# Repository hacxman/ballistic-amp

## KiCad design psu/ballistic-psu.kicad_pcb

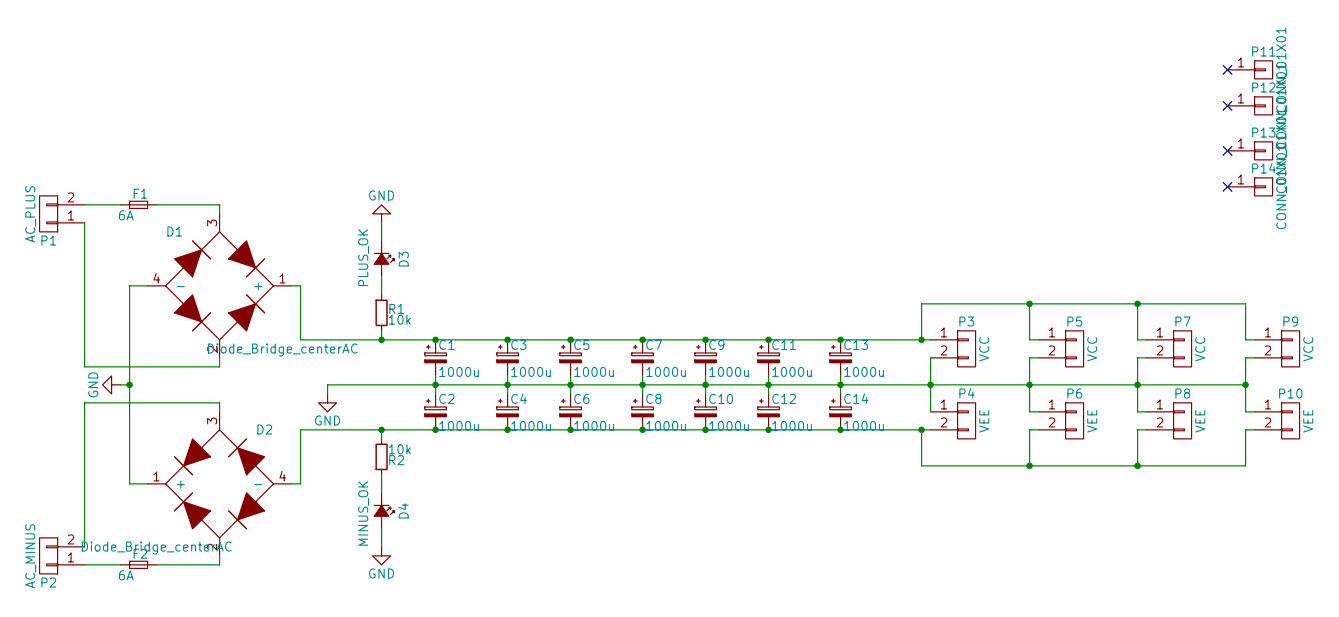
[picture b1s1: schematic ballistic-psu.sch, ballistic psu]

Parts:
C1, C2, C3, C4, C5, C6, C7, C8, C9, C10, C11, C12, C13, C14: 1000u; C_Radial_D18_L36_P7.5
D1, D2: Diode_Bridge_centerAC; GSIB
D3: PLUS_OK; LED-5MM
D4: MINUS_OK; LED-5MM
F1, F2: 6A; Fuseholder5x20_horiz_SemiClosed_Casing10x25mm
P1: AC_PLUS; TerminalBlock_Pheonix_MKDS1.5-2pol
P2: AC_MINUS; TerminalBlock_Pheonix_MKDS1.5-2pol
P3, P5, P7, P9: VCC; TerminalBlock_Pheonix_MKDS1.5-2pol
P4, P6, P8, P10: VEE; TerminalBlock_Pheonix_MKDS1.5-2pol
P11, P12, P13, P14: CONN_01X01; MountingHole_3mm
R1, R2: 10k; Resistor_Horizontal_RM10mm

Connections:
GND: C1.2, C2.1, C3.2, C4.1, C5.2, C6.1, C7.2, C8.1, C9.2, C10.1, C11.2, C12.1, C13.2, C14.1, D1.4 (-), D2.1 (+), D3.1 (K), D4.2 (A), P3.2, P4.1, P5.2, P6.1, P7.2, P8.1, P9.2, P10.1
unnamed: C1.1, C3.1, C5.1, C7.1, C9.1, C11.1, C13.1, D1.1 (+), P3.1, P5.1, P7.1, P9.1, R1.2
unnamed: C2.2, C4.2, C6.2, C8.2, C10.2, C12.2, C14.2, D2.4 (-), P4.2, P6.2, P8.2, P10.2, R2.2
unnamed: D1.2, P1.1
unnamed: D1.3, F1.2
unnamed: D2.2, F2.2
unnamed: D2.3, P2.2
unnamed: D3.2 (A), R1.1
unnamed: D4.1 (K), R2.1
unnamed: F1.1, P1.2
unnamed: F2.1, P2.1

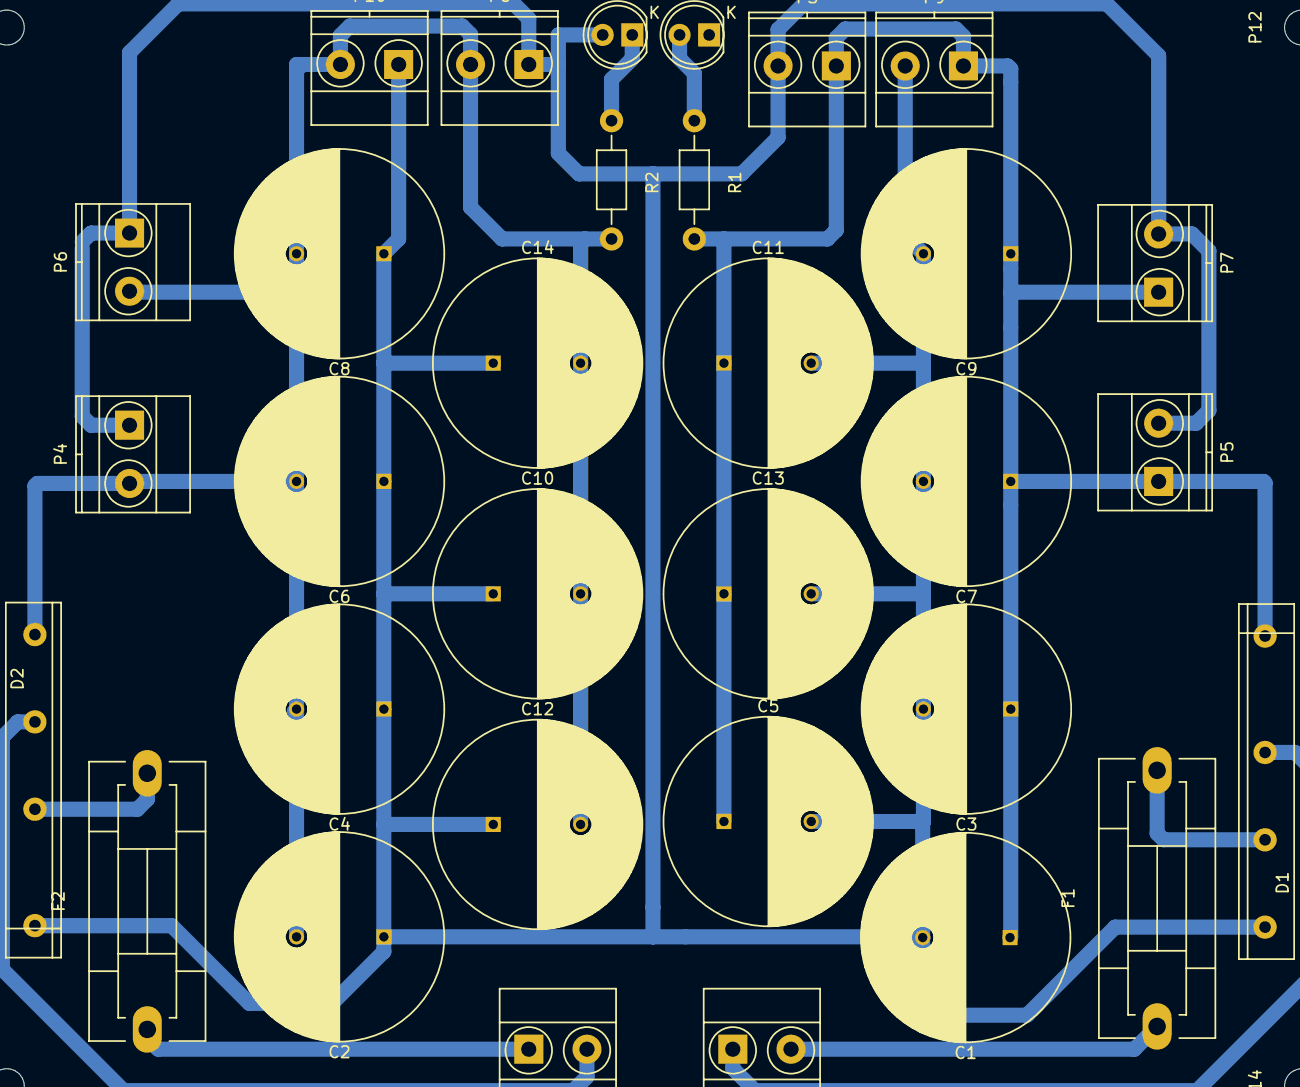
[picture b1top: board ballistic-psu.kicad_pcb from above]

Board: 2 copper layers, 36 parts (0 on the bottom side), 11 nets.

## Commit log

2016-12-10 first
